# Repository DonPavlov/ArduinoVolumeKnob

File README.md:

This is an Arduino Pro Micro Volume Knob following the following example.

https://www.heise.de/select/make/2019/2/1556001541578799

Troubleshooting:
If your Pro Micro does not want to be programmed do the following:

Verify the correct upload port and set it in the platformio.ini file.
(Unplug the device check the which devices are under /dev/tty:
    ls /dev/tty*
And replug the device)

If programming still fails, wait while it is uploading and use something metal and connect RST and GND pin for a short while. This reset should be enough to upload the latest Arduino files onto the Board and should work now after that without an Reset.

PCB Layout
------------------

The PCB itself was designed in KiCaD and has the following design:

It uses additional features of a possible reset button.
And a free toggle Button to connect and do interesting stuff. (Select in grub the used os to boot or other such things)

TODO
-------------------

* Implement functionality to select windows in grub (arrow down, arrow down, enter) after device was switched on after 5 seconds it will trigger (depends on grub timeout)
    * Do this only if the switch was flipped into the windows position
* Better documentation

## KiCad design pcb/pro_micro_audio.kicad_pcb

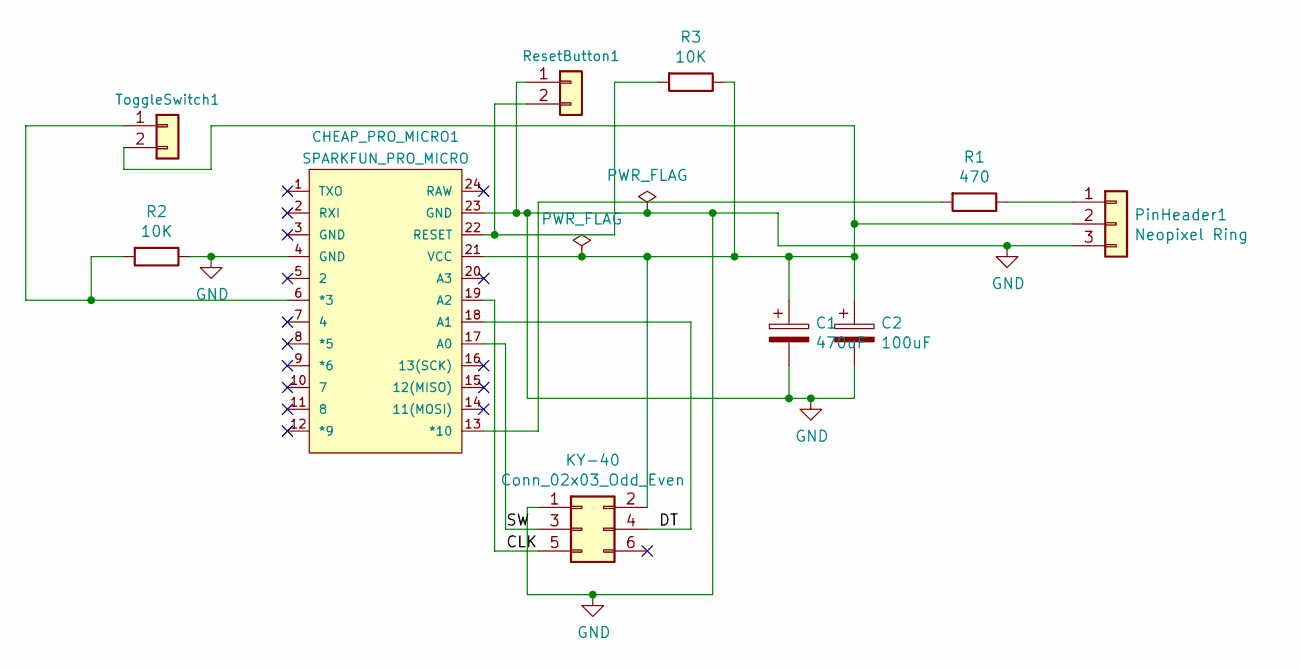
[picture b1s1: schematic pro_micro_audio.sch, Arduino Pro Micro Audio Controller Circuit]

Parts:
C1: 470uF; C_Radial_D16.0mm_H25.0mm_P7.50mm
C2: 100uF; C_Radial_D5.0mm_H11.0mm_P2.00mm
CHEAP_PRO_MICRO1: SPARKFUN_PRO_MICRO
KY-40: Conn_02x03_Odd_Even; PinHeader_2x03_P2.54mm_Vertical
PinHeader1: Neopixel Ring; PinHeader_1x03_P2.54mm_Vertical
R1: 470; R_Axial_DIN0207_L6.3mm_D2.5mm_P10.16mm_Horizontal
R2, R3: 10K; R_Axial_DIN0207_L6.3mm_D2.5mm_P10.16mm_Horizontal
ResetButton1: Connector_Generic:Conn_01x02; PinHeader_1x02_P2.54mm_Vertical
ToggleSwitch1: Connector_Generic:Conn_01x02; PinHeader_1x02_P2.54mm_Vertical

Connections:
/CLK: CHEAP_PRO_MICRO1.19 (A2), KY-40.5
/DT: CHEAP_PRO_MICRO1.18 (A1), KY-40.4
/SW: CHEAP_PRO_MICRO1.17 (A0), KY-40.3
GND: C1.2, C2.2, CHEAP_PRO_MICRO1.4 (GND), CHEAP_PRO_MICRO1.23 (GND), KY-40.1, PinHeader1.3, R2.1, ResetButton1.1
unnamed: C1.1, C2.1, CHEAP_PRO_MICRO1.21 (VCC), KY-40.2, PinHeader1.2, R3.1, ToggleSwitch1.2
unnamed: CHEAP_PRO_MICRO1.6 (*3), R2.2, ToggleSwitch1.1
unnamed: CHEAP_PRO_MICRO1.13 (*10), R1.2
unnamed: CHEAP_PRO_MICRO1.22 (RESET), R3.2, ResetButton1.2
unnamed: PinHeader1.1, R1.1

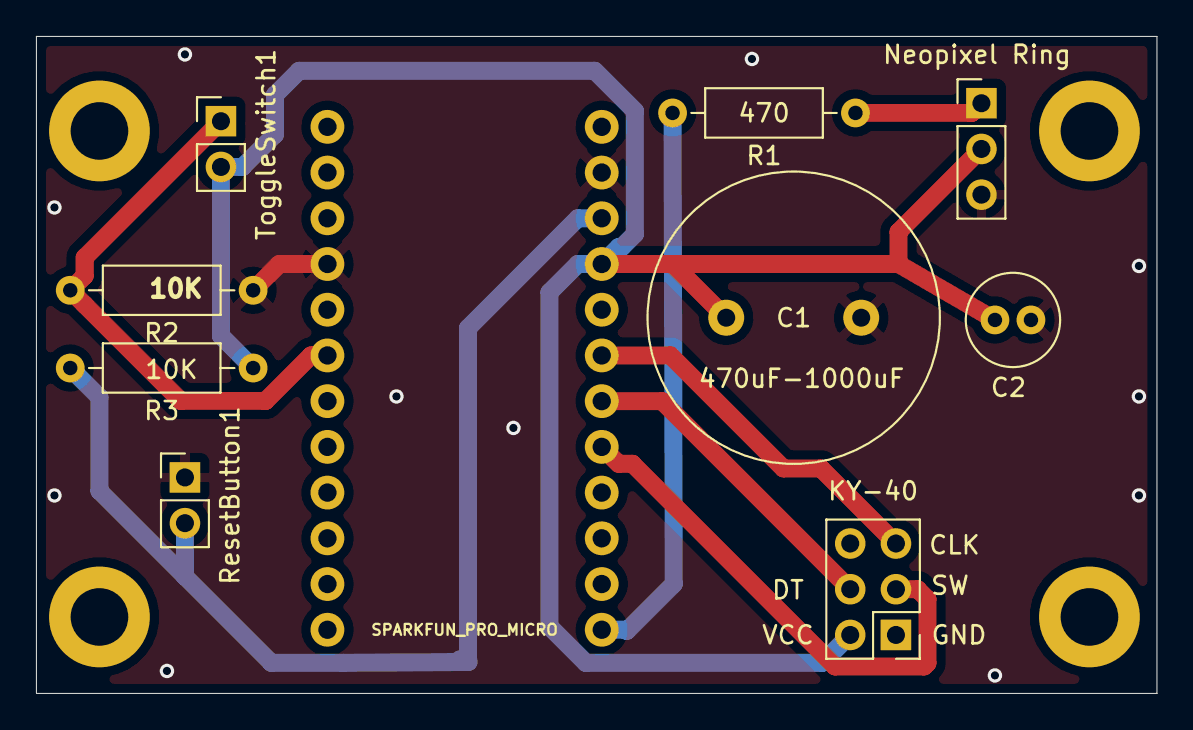
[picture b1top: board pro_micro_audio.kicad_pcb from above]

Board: 2 copper layers, 62.2 x 36.5 mm, 10 parts (0 on the bottom side), 9 nets.

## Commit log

2019-09-11 Stub Readme file
2019-09-11 Use HID-Keyboard library for testing.
2019-09-11 Update with latest listing from heise/make
2019-09-11 update libraries to specific version for platformio
2019-09-11 disable rx tx leds
2019-09-12 update led number
2019-09-14 fix timerone error with led not stopping
2019-09-14 remove vibration motor traces completely
2019-09-28 update for latest pcb changes
2019-10-01 Update the image
2019-10-01 Update Readme with more information
2019-10-01 add kicad files
2019-10-01 More readme, more images
2019-10-23 Readout Digitalpin
2019-10-23 Add keyboard commands layout
2019-10-23 Update Keyboard stuff
    Now possible to select Windows as third entry inside grub
2019-10-26 adjust timeout
2019-12-15 add png img
2019-12-22 add christmas color mode
2019-12-22 remove unused cad files
2020-04-11 updated the code to be more toddler friendly and fun
2020-11-07 update stuffs
